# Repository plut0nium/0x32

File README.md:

# >**0x32**_ "Brussels Waffle". Lighter & Crispier. 
A 40% low-profile & wireless ortholinear board ⌨

> **Warning / Disclaimer**  
> These files are provided as a reference for designing keyboard PCBs, without liability and without any guarantees regarding functionality. 
> Although prototypes have been built and tested, errors may still be present.
> It is not advised to use them in your own project without electronics knowledge.

More pictures: <https://imgur.com/a/yrJpx6d>

## Features

 * Powered by nRF52840 SoC
   * 32bit, 64MHz, 1Mo flash
   * Bluetooth 5.0
 * Advanced LiPo battery charging circuit (_see comments below_)
 * USB Type-C with ESD protection
 * Designed for Kailh PG1350 "Choc" switches
   * Uses the smaller choc 18×17mm pitch
   * Only 1u alphas & mods (+ 1.5 or 2u split spacebar)
 * Supports 1 centered (thumb) roller encoder 
 * Powered by ZMK

## Comments / Design discussion

The battery and power management circuitry was designed around the following ICs:

 * BQ24075 for LiPo charging
 * TPS63031 for (3.3V) voltage regulation

This can be considered as a relatively advanced design, in comparison with the "classical" TP4056 + DW01A + LDO combination, but is also far from perfect:

This was taken as a learning opportunity, and performance improvement (in terms of power efficiency), if any, has not been assessed, and is probably not worth the extra cost and design complexity.
This is especially true for the use of a Buck-Boost converter, as the gain in extra power recovery from the battery should be limited (to max 5% capacity wrt a simpler Buck, or even a good quality LDO linear regulator).

I would however always recommend the use of high-quality components when it comes to LiPo battery management...

Other design limitations:
 * The lack of a LED tied to an IO of the MCU module, making it impossible to (externally) identify when the device is in bootloader mode.
 * The two available LEDs are used for power management / battery charging are sandwiched between the PCB and the switch plate, thus not replaceable once the board is assembled.

No PCBA files are provided since the few proto boards were assembled by hand (human PnP and reflow oven).

## Battery

The cutout in the PCB has been designed to accomodate a **402535** LiPo battery (~300mAh), sandwiched between switch & bottom plates.

## Layout

## License

Copyright Charles Fourneau, 2021.

This source describes Open Hardware and is licensed under the _CERN-OHL-W_ v2

You may redistribute and modify this documentation and make products using it under the terms   of the CERN-OHL-W v2 (<https:/cern.ch/cern-ohl>). This documentation is distributed WITHOUT ANY EXPRESS OR IMPLIED WARRANTY, INCLUDING OF MERCHANTABILITY, SATISFACTORY QUALITY AND FITNESS FOR A PARTICULAR PURPOSE. Please see the CERN-OHL-W v2 for applicable conditions.

## Credits

0x32 is a new design but inspired by boards like:
 - Hadron by Ishtob
 - Boardwalk by AlexAtPanc, Shensmobile & others
 - Planck (Light) by OLKB
 - Pancake by Spaceman
 - ...some if my previous designs 😄

And special thanks to [ebastler](https://github.com/ebastler) for providing information I used as reference design for Holyiot modules.

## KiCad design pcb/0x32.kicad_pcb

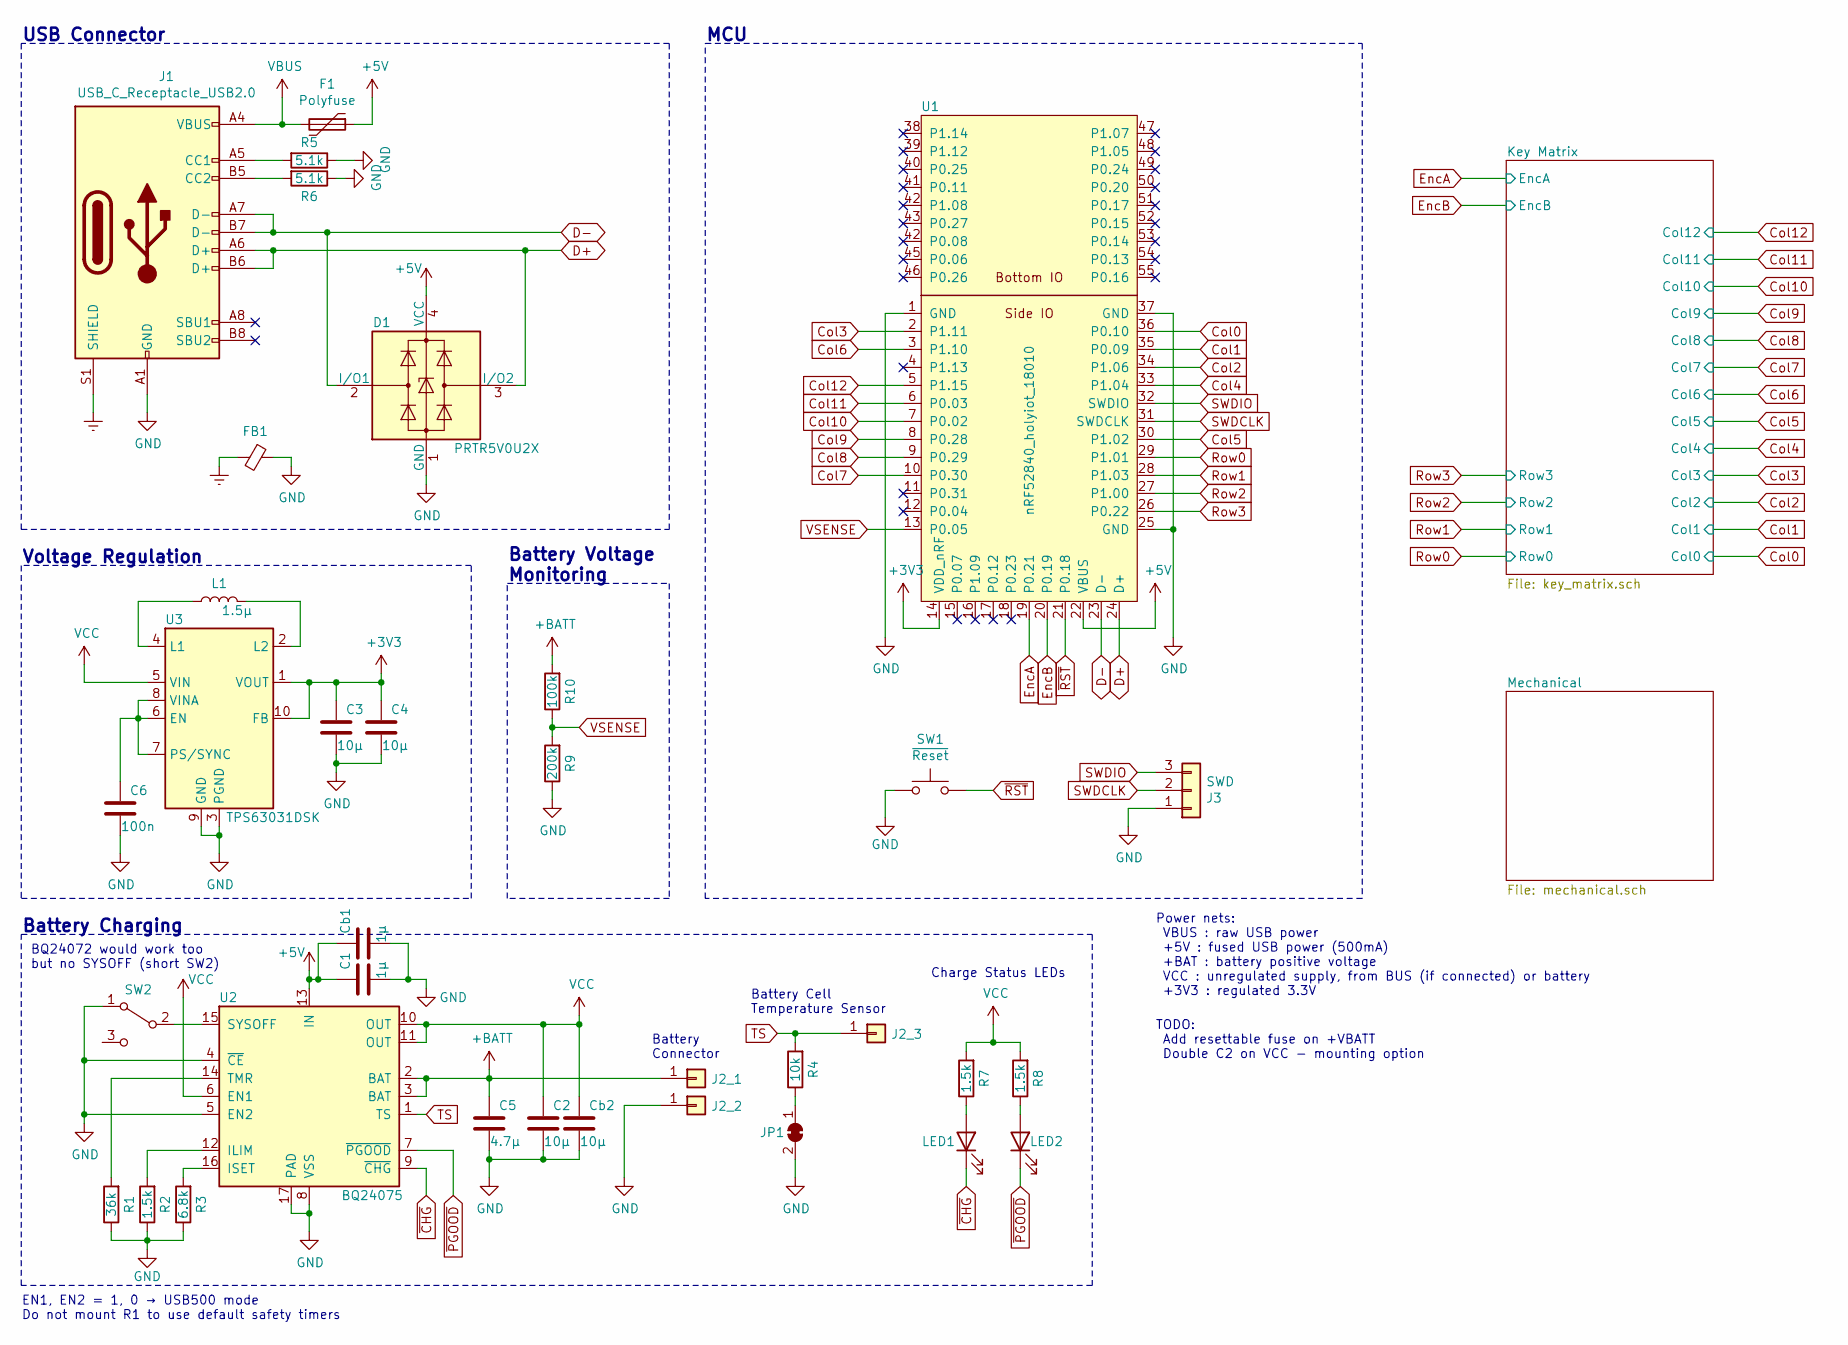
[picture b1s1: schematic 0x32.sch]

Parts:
C1: 1µ; C_0603_1608Metric; LCSC C29823
C2, C3, C4: 10µ; C_0603_1608Metric; LCSC C29823
C5: 4.7µ; C_0603_1608Metric; LCSC C29823
C6: 100n; C_0603_1608Metric; LCSC C29823
Cb1: 1µ; C_0603_1608Metric; LCSC C29823
Cb2: 10µ; C_0603_1608Metric; LCSC C29823
D1: PRTR5V0U2X; SOT-143; LCSC C78442
F1: Polyfuse; Fuse_0805_2012Metric; LCSC C135338
FB1: Ferrite_Bead_Small; R_0805_2012Metric
J1: USB_C_Receptacle_USB2.0; USB_C_Receptacle_HRO_TYPE-C-31-M-14
J2_1, J2_2, J2_3: Conn_01x01; SolderPad_4.0x2.0mm
J3: SWD; PinHeader_1x03_P2.54mm_Vertical
JP1: SolderJumper_2_Bridged; SolderJumper-2_RoundedPad_0.8x1.0mm
L1: 1.5µ; L_1008_2520Metric
LED1, LED2: LED; LED_0603_1608Metric
R1: 36k; R_0603_1608Metric; LCSC C23186
R2, R7, R8: 1.5k; R_0603_1608Metric; LCSC C23186
R3: 6.8k; R_0603_1608Metric; LCSC C23186
R4: 10k; R_0603_1608Metric; LCSC C23186
R5, R6: 5.1k; R_0603_1608Metric; LCSC C23186
R9: 200k; R_0603_1608Metric; LCSC C23186
R10: 100k; R_0603_1608Metric; LCSC C23186
SW1: ~Reset; TS-1186E-X-A; LCSC C318884
SW2: SW_SPDT; SW_SPDT_SMD_PCM12
U1: nRF52840_holyiot_18010; nRF52840_holyiot_18010_SideOnly
U2: BQ24075; VQFN-16-1EP_3x3mm_P0.5mm_EP1.8x1.8mm
U3: TPS63031DSK; WSON-10-1EP_2.5x2.5mm_P0.5mm_EP1.2x2mm

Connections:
+3V3: C3.1, C4.1, U1.14 (VDD_nRF), U3.1 (VOUT), U3.10 (FB)
+5V: C1.1, Cb1.1, D1.4 (VCC), F1.1, U1.22 (VBUS), U2.13 (IN)
+BATT: C5.1, J2_1.1, R10.2, U2.2 (BAT), U2.3 (BAT)
Col0: U1.36 (P0.10); also elsewhere on the board
Col1: U1.35 (P0.09); also elsewhere on the board
Col2: U1.34 (P1.06); also elsewhere on the board
Col3: U1.2 (P1.11); also elsewhere on the board
Col4: U1.33 (P1.04); also elsewhere on the board
Col5: U1.30 (P1.02); also elsewhere on the board
Col6: U1.3 (P1.10); also elsewhere on the board
Col7: U1.10 (P0.30); also elsewhere on the board
Col8: U1.9 (P0.29); also elsewhere on the board
Col9: U1.8 (P0.28); also elsewhere on the board
Col10: U1.7 (P0.02); also elsewhere on the board
Col11: U1.6 (P0.03); also elsewhere on the board
Col12: U1.5 (P1.15); also elsewhere on the board
D+: D1.3 (I/O2), J1.A6 (D+), J1.B6 (D+), U1.24 (D+)
D-: D1.2 (I/O1), J1.A7 (D-), J1.B7 (D-), U1.23 (D-)
Earth: FB1.2, J1.S1 (SHIELD)
EncA: U1.19 (P0.21); also elsewhere on the board
EncB: U1.20 (P0.19); also elsewhere on the board
GND: C1.2, C2.2, C3.2, C4.2, C5.2, C6.2, Cb1.2, Cb2.2, D1.1 (GND), FB1.1, J1.A1 (GND), J1.A12 (GND), J1.B1 (GND), J1.B12 (GND), J2_2.1, J3.1, JP1.2 (B), R1.1, R2.1, R3.1, R5.1, R6.1, R9.1, SW1.1, SW2.1 (A), U1.1 (GND), U1.25 (GND), U1.37 (GND), U2.4 (~CE), U2.5 (EN2), U2.8 (VSS), U2.17 (PAD), U3.3 (PGND), U3.9 (GND), U3.11 (PGND); also elsewhere on the board
unnamed: C6.1, U3.6 (EN), U3.7 (PS/SYNC), U3.8 (VINA)
unnamed: J1.A5 (CC1), R5.2
unnamed: J1.B5 (CC2), R6.2
unnamed: JP1.1 (A), R4.1
unnamed: L1.1, U3.4 (L1)
unnamed: L1.2, U3.2 (L2)
unnamed: LED1.2 (A), R7.1
unnamed: LED2.2 (A), R8.1
unnamed: R1.2, U2.14 (TMR)
unnamed: R2.2, U2.12 (ILIM)
unnamed: R3.2, U2.16 (ISET)
unnamed: SW2.2 (B), U2.15 (SYSOFF)
Row0: U1.29 (P1.01); also elsewhere on the board
Row1: U1.28 (P1.03); also elsewhere on the board
Row2: U1.27 (P1.00); also elsewhere on the board
Row3: U1.26 (P0.22); also elsewhere on the board
SWDCLK: J3.2, U1.31 (SWDCLK)
SWDIO: J3.3, U1.32 (SWDIO)
TS: J2_3.1, R4.2, U2.1 (TS)
VBUS: F1.2, J1.A4 (VBUS), J1.A9 (VBUS), J1.B4 (VBUS), J1.B9 (VBUS)
VCC: C2.1, Cb2.1, R7.2, R8.2, U2.6 (EN1), U2.10 (OUT), U2.11 (OUT), U3.5 (VIN)
VSENSE: R9.2, R10.1, U1.13 (P0.05)
~CHG: LED1.1 (K), U2.9 (~CHG)
~PGOOD: LED2.1 (K), U2.7 (~PGOOD)
~RST: SW1.2, U1.21 (P0.18)

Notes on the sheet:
Battery Charging
Voltage Regulation
USB Connector
Power nets: VBUS : raw USB power +5V : fused USB power (500mA) +BAT : battery positive voltage VCC : unregulated supply, from BUS (if connected) or battery +3V3 : regulated 3.3V
Battery Cell Temperature Sensor
Charge Status LEDs
Battery Voltage Monitoring
MCU
BQ24072 would work too but no SYSOFF (short SW2)
TODO: Add resettable fuse on +VBATT Double C2 on VCC - mounting option
Battery Connector
EN1, EN2 = 1, 0 → USB500 mode Do not mount R1 to use default safety timers

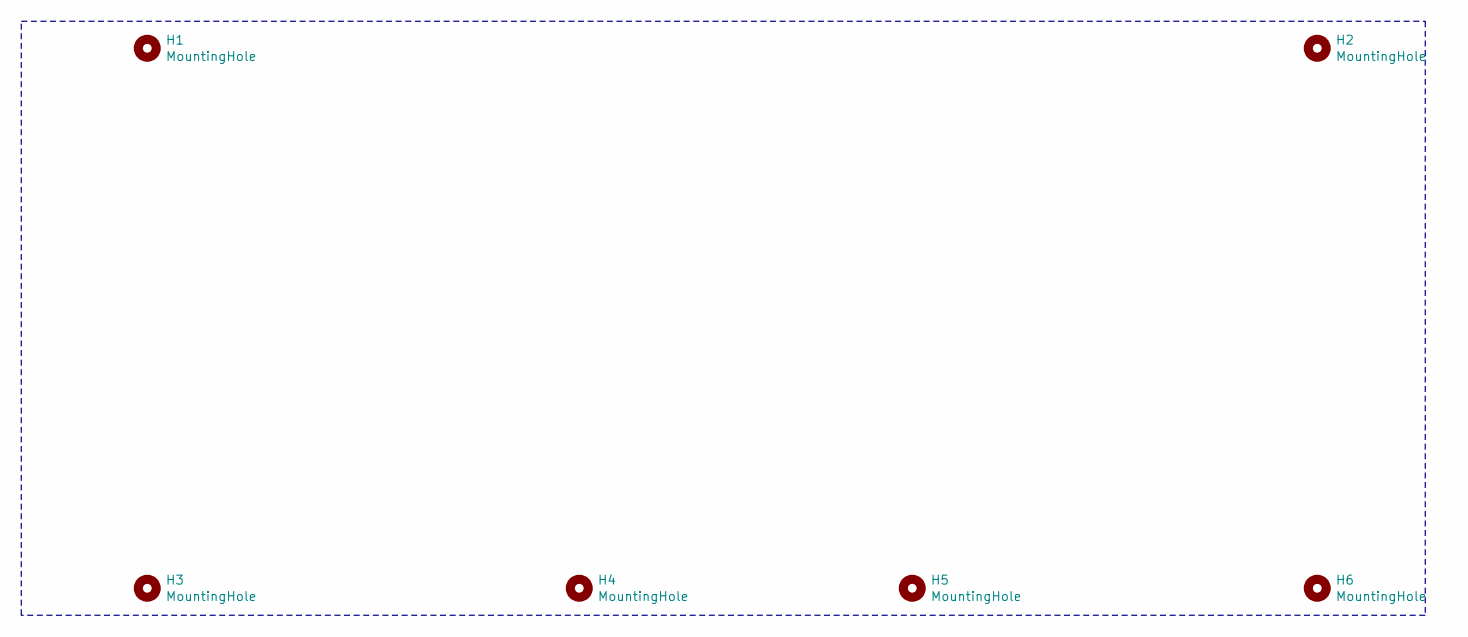
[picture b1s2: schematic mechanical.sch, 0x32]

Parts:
H1, H2, H3, H4, H5, H6: MountingHole; MountingHole_2.5mm

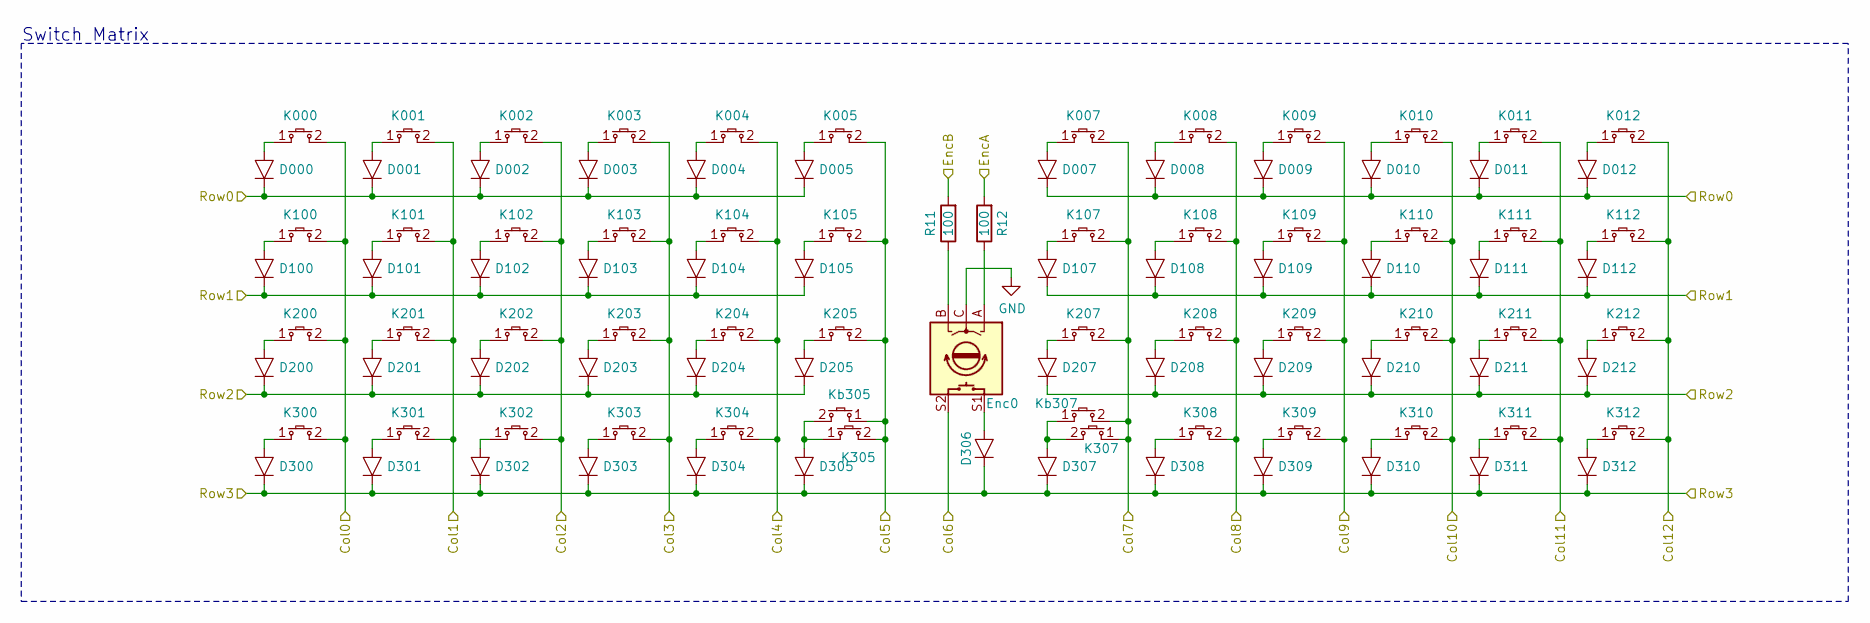
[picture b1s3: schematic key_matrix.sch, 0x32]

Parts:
D000, D001, D002, D003, D004, D005, D007, D008, D009, D010, D011, D012, D100, D101, D102, D103, D104, D105, D107, D108, D109, D110, D111, D112, D200, D201, D202, D203, D204, D205, D207, D208, D209, D210, D211, D212, D300, D301, D302, D303, D304, D305, D307, D308, D309, D310, D311, D312: Diode; D_MiniMELF
D306: Diode; D_MiniMELF; LCSC C2128
Enc0: Rotary_Encoder_Switch; RollerEncoder_Panasonic_EVQWGD001
K000, K001, K002, K003, K004, K005, K007, K008, K009, K010, K011, K012, K100, K101, K102, K103, K104, K105, K107, K108, K109, K110, K111, K112, K200, K201, K202, K203, K204, K205, K207, K208, K209, K210, K211, K212, K300, K301, K302, K303, K304, K308, K309, K310, K311, K312: Key_Switch; Kailh_PG1350_Choc-1U-NoLED
K305, K307: Key_Switch; Kailh_PG1350_Choc-2U-NoLED
Kb305, Kb307: Key_Switch; Kailh_PG1350_Choc-1.5U-NoLED
R11, R12: 100; R_0603_1608Metric

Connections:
Col0: K000.2, K100.2, K200.2, K300.2; also elsewhere on the board
Col1: K001.2, K101.2, K201.2, K301.2; also elsewhere on the board
Col2: K002.2, K102.2, K202.2, K302.2; also elsewhere on the board
Col3: K003.2, K103.2, K203.2, K303.2; also elsewhere on the board
Col4: K004.2, K104.2, K204.2, K304.2; also elsewhere on the board
Col5: K005.2, K105.2, K205.2, K305.2, Kb305.1; also elsewhere on the board
Col6: Enc0.S2; also elsewhere on the board
Col7: K007.2, K107.2, K207.2, K307.1, Kb307.2; also elsewhere on the board
Col8: K008.2, K108.2, K208.2, K308.2; also elsewhere on the board
Col9: K009.2, K109.2, K209.2, K309.2; also elsewhere on the board
Col10: K010.2, K110.2, K210.2, K310.2; also elsewhere on the board
Col11: K011.2, K111.2, K211.2, K311.2; also elsewhere on the board
Col12: K012.2, K112.2, K212.2, K312.2; also elsewhere on the board
EncA: R12.2; also elsewhere on the board
EncB: R11.2; also elsewhere on the board
GND: Enc0.C; also elsewhere on the board
unnamed: D000.2 (A), K000.1
unnamed: D001.2 (A), K001.1
unnamed: D002.2 (A), K002.1
unnamed: D003.2 (A), K003.1
unnamed: D004.2 (A), K004.1
unnamed: D005.2 (A), K005.1
unnamed: D007.2 (A), K007.1
unnamed: D008.2 (A), K008.1
unnamed: D009.2 (A), K009.1
unnamed: D010.2 (A), K010.1
unnamed: D011.2 (A), K011.1
unnamed: D012.2 (A), K012.1
unnamed: D100.2 (A), K100.1
unnamed: D101.2 (A), K101.1
unnamed: D102.2 (A), K102.1
unnamed: D103.2 (A), K103.1
unnamed: D104.2 (A), K104.1
unnamed: D105.2 (A), K105.1
unnamed: D107.2 (A), K107.1
unnamed: D108.2 (A), K108.1
unnamed: D109.2 (A), K109.1
unnamed: D110.2 (A), K110.1
unnamed: D111.2 (A), K111.1
unnamed: D112.2 (A), K112.1
unnamed: D200.2 (A), K200.1
unnamed: D201.2 (A), K201.1
unnamed: D202.2 (A), K202.1
unnamed: D203.2 (A), K203.1
unnamed: D204.2 (A), K204.1
unnamed: D205.2 (A), K205.1
unnamed: D207.2 (A), K207.1
unnamed: D208.2 (A), K208.1
unnamed: D209.2 (A), K209.1
unnamed: D210.2 (A), K210.1
unnamed: D211.2 (A), K211.1
unnamed: D212.2 (A), K212.1
unnamed: D300.2 (A), K300.1
unnamed: D301.2 (A), K301.1
unnamed: D302.2 (A), K302.1
unnamed: D303.2 (A), K303.1
unnamed: D304.2 (A), K304.1
unnamed: D305.2 (A), K305.1, Kb305.2
unnamed: D306.2 (A), Enc0.S1
unnamed: D307.2 (A), K307.2, Kb307.1
unnamed: D308.2 (A), K308.1
unnamed: D309.2 (A), K309.1
unnamed: D310.2 (A), K310.1
unnamed: D311.2 (A), K311.1
unnamed: D312.2 (A), K312.1
unnamed: Enc0.A, R12.1
unnamed: Enc0.B, R11.1
Row0: D000.1 (K), D001.1 (K), D002.1 (K), D003.1 (K), D004.1 (K), D005.1 (K), D007.1 (K), D008.1 (K), D009.1 (K), D010.1 (K), D011.1 (K), D012.1 (K); also elsewhere on the board
Row1: D100.1 (K), D101.1 (K), D102.1 (K), D103.1 (K), D104.1 (K), D105.1 (K), D107.1 (K), D108.1 (K), D109.1 (K), D110.1 (K), D111.1 (K), D112.1 (K); also elsewhere on the board
Row2: D200.1 (K), D201.1 (K), D202.1 (K), D203.1 (K), D204.1 (K), D205.1 (K), D207.1 (K), D208.1 (K), D209.1 (K), D210.1 (K), D211.1 (K), D212.1 (K); also elsewhere on the board
Row3: D300.1 (K), D301.1 (K), D302.1 (K), D303.1 (K), D304.1 (K), D305.1 (K), D306.1 (K), D307.1 (K), D308.1 (K), D309.1 (K), D310.1 (K), D311.1 (K), D312.1 (K); also elsewhere on the board

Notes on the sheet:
Switch Matrix

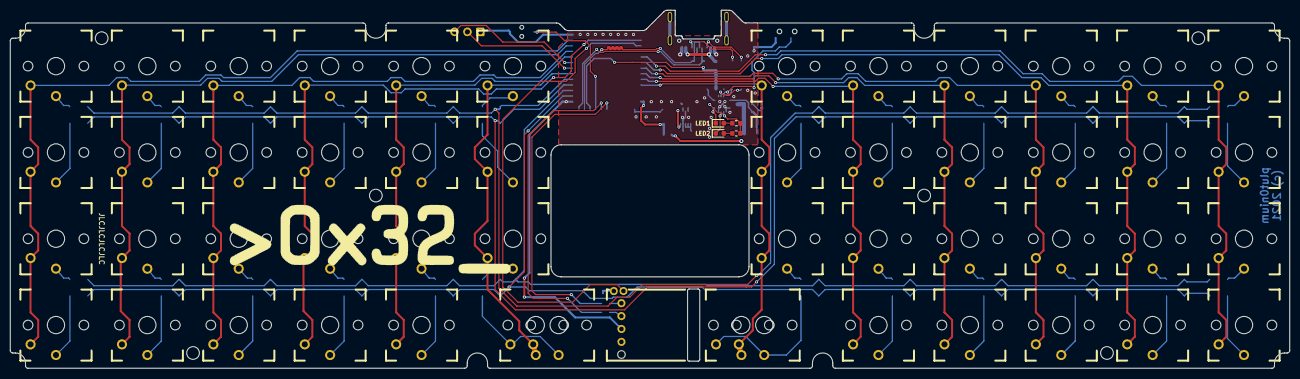
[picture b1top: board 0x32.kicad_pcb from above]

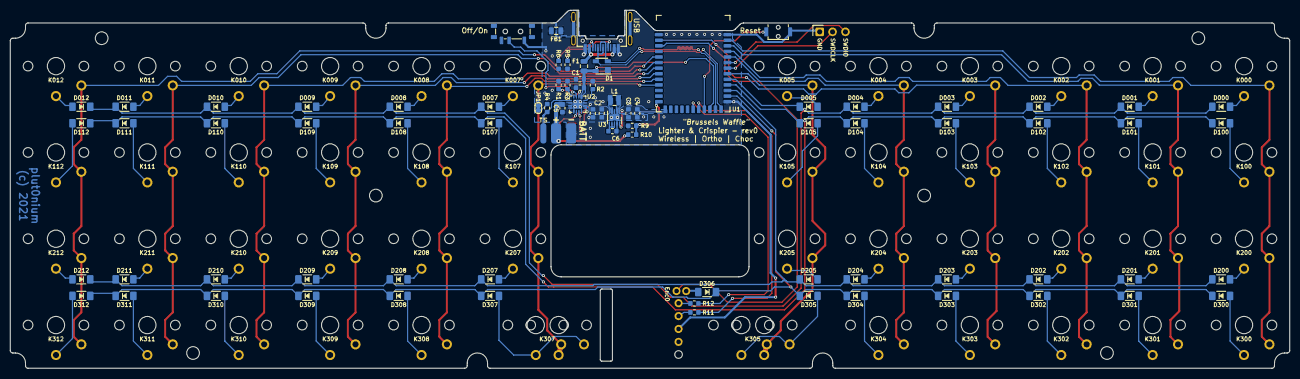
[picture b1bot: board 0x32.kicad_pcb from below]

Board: 2 copper layers, 252.0 x 70.5 mm, 143 parts (82 on the bottom side), 98 nets.

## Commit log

2021-08-22 0x32 Final PCB - rev0
2021-08-22 Add BOM for human PnP
2021-08-22 Add (clean) switch and bottom plates
2021-08-22 Update README and documentation.

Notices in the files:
pcb/0x32.kicad_pcb:
(c) 2021
